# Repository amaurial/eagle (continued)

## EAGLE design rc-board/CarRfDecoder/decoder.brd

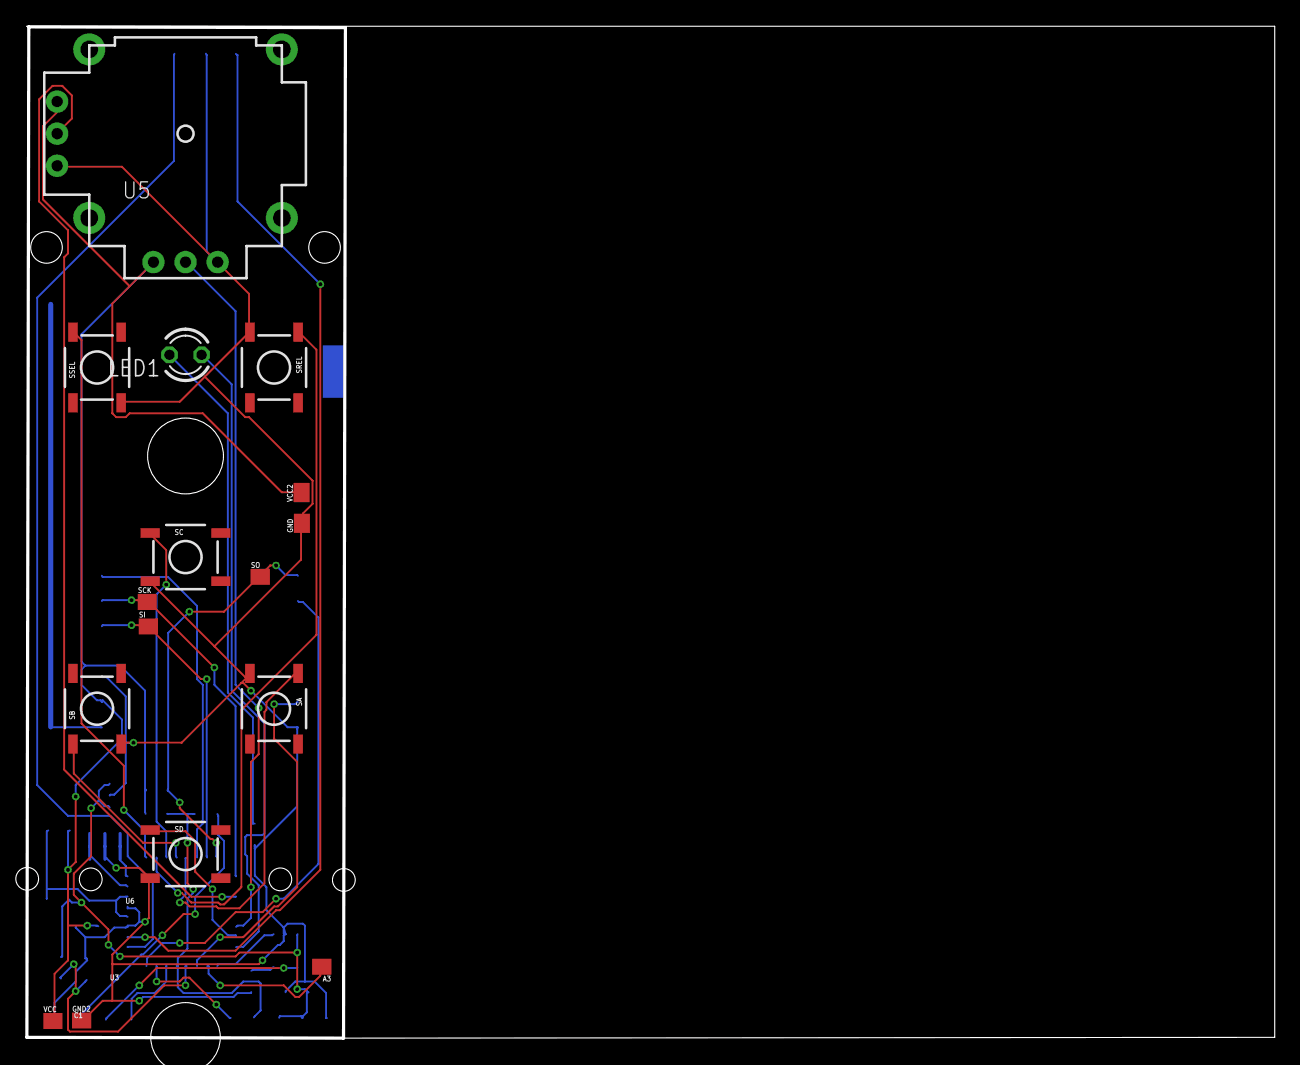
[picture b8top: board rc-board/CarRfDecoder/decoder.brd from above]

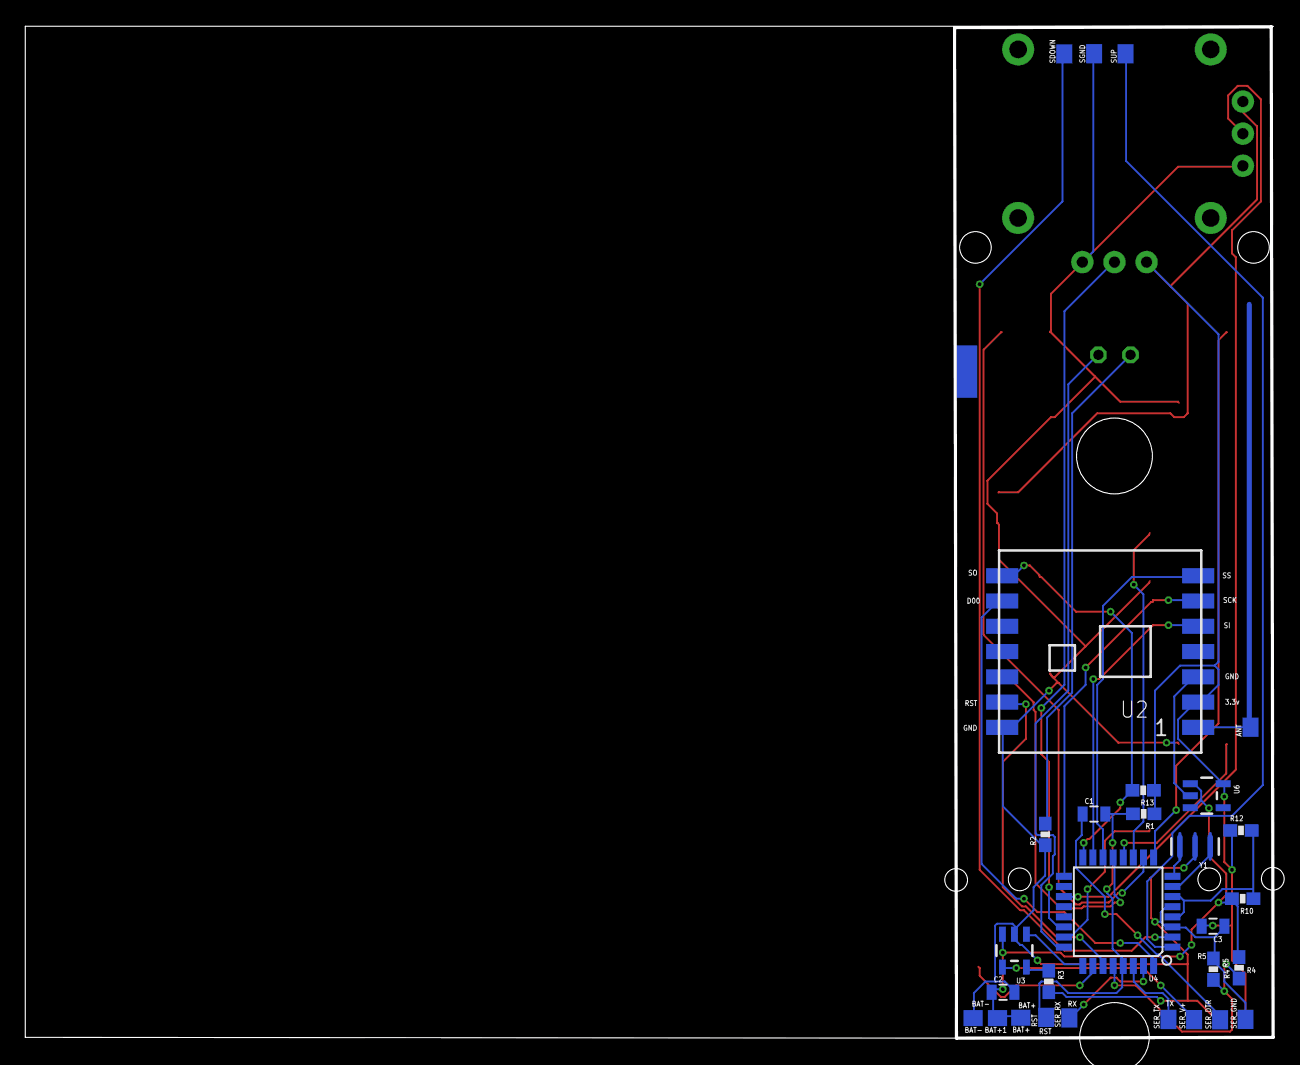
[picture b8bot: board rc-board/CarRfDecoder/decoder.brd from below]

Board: 2 copper layers, 98.7 x 80.1 mm, 45 parts (29 on the bottom side), 34 nets.

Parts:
A3: SMD1,27-2,54
ANT: SMD1,27-2,54
BAT+, BAT+1: SMD1,27-2,54
BAT-: SMD1,27-2,54
C1: 0.1uF; 0805
C2, C3: 4.7uF; 0805
GND, GND2: SMD1,27-2,54
LED1: LED3MM
R1, R13: 10k; 0603-RES
R2: 200; 0603-RES
R3, R4, R5: 2K; 0603-RES
R10, R12: 0; 0603-RES
RST: SMD1,27-2,54
SA: TAC_SWITCHSMD; TACTILE-SWITCH-SMD
SB: TAC_SWITCHSMD; TACTILE-SWITCH-SMD
SC: TAC_SWITCHSMD; TACTILE-SWITCH-SMD
SCK: SMD1,27-2,54
SD: TAC_SWITCHSMD; TACTILE-SWITCH-SMD
SDOWN: SMD1,27-2,54
SER_DTR: SMD1,27-2,54
SER_GND: SMD1,27-2,54
SER_RX: SMD1,27-2,54
SER_TX: SMD1,27-2,54
SER_V+: SMD1,27-2,54
SGND: SMD1,27-2,54
SI: SMD1,27-2,54
SO: SMD1,27-2,54
SREL: TAC_SWITCHSMD; TACTILE-SWITCH-SMD
SSEL: TAC_SWITCHSMD; TACTILE-SWITCH-SMD
SUP: SMD1,27-2,54
U2: RFM69CW; RFM69CW-XXXS2
U3: MCP73831; SOT23-5
U4: ATMEGA328P; TQFP32-08
U5: JOYSTICKPTH; JOYSTICK
U6: MIC5219 3.3V; SOT23-5
VCC, VCC2: SMD1,27-2,54
Y1: 16MHZ; RESONATOR-SMD

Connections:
A0: SD.1, U4.23
A1: LED1.A, U4.24
A2: U3.1, U4.25
A3: A3.1, U4.26
A4: U2.13, U4.27
A5: R4.1, R5.2, U4.28
A6: U4.19, U5.V2
A7: U4.22, U5.H2
BAT+: BAT+.1, BAT+1.1, C2.1, R4.2, R10.2, U3.3, U6.1, U6.3
D2: U2.9, U4.32
D3: SUP.1, U4.1
D4: SDOWN.1, U4.2
D5: SSEL.2, U4.9
D6: SREL.1, U4.10
D7: SC.1, U4.11
D8: SB.1, U4.12
D9: SA.1, U4.13
GND: BAT-.1, C2.2, C3.1, GND.1, GND2.1, R2.1, R3.2, R5.1, SA.3, SB.3, SC.3, SD.3, SER_GND.1, SGND.1, SREL.3, SSEL.3, U2.3, U2.14, U3.2, U4.3, U4.5, U5.H3, U5.V3, U6.2, Y1.2
MISO: R13.2, SO.1, U2.8, U4.16
MOSI: SI.1, U2.5, U4.15
unnamed: ANT.1, U2.1
unnamed: U4.7, Y1.1
unnamed: C1.1, SER_DTR.1
unnamed: U4.8, Y1.3
unnamed: C1.2, R1.2, RST.1, U4.29
unnamed: R10.1, R12.2, U4.4, U4.6
unnamed: SER_V+.1, U3.4
unnamed: R3.1, U3.5
unnamed: LED1.K, R2.2
RX: SER_TX.1, U4.30
SCK: SCK.1, U2.6, U4.17
SS: U2.7, U4.14
TX: SER_RX.1, U4.31
VCC: C3.2, R1.1, R12.1, R13.1, U2.2, U5.H1, U5.V1, U6.5, VCC.1, VCC2.1
